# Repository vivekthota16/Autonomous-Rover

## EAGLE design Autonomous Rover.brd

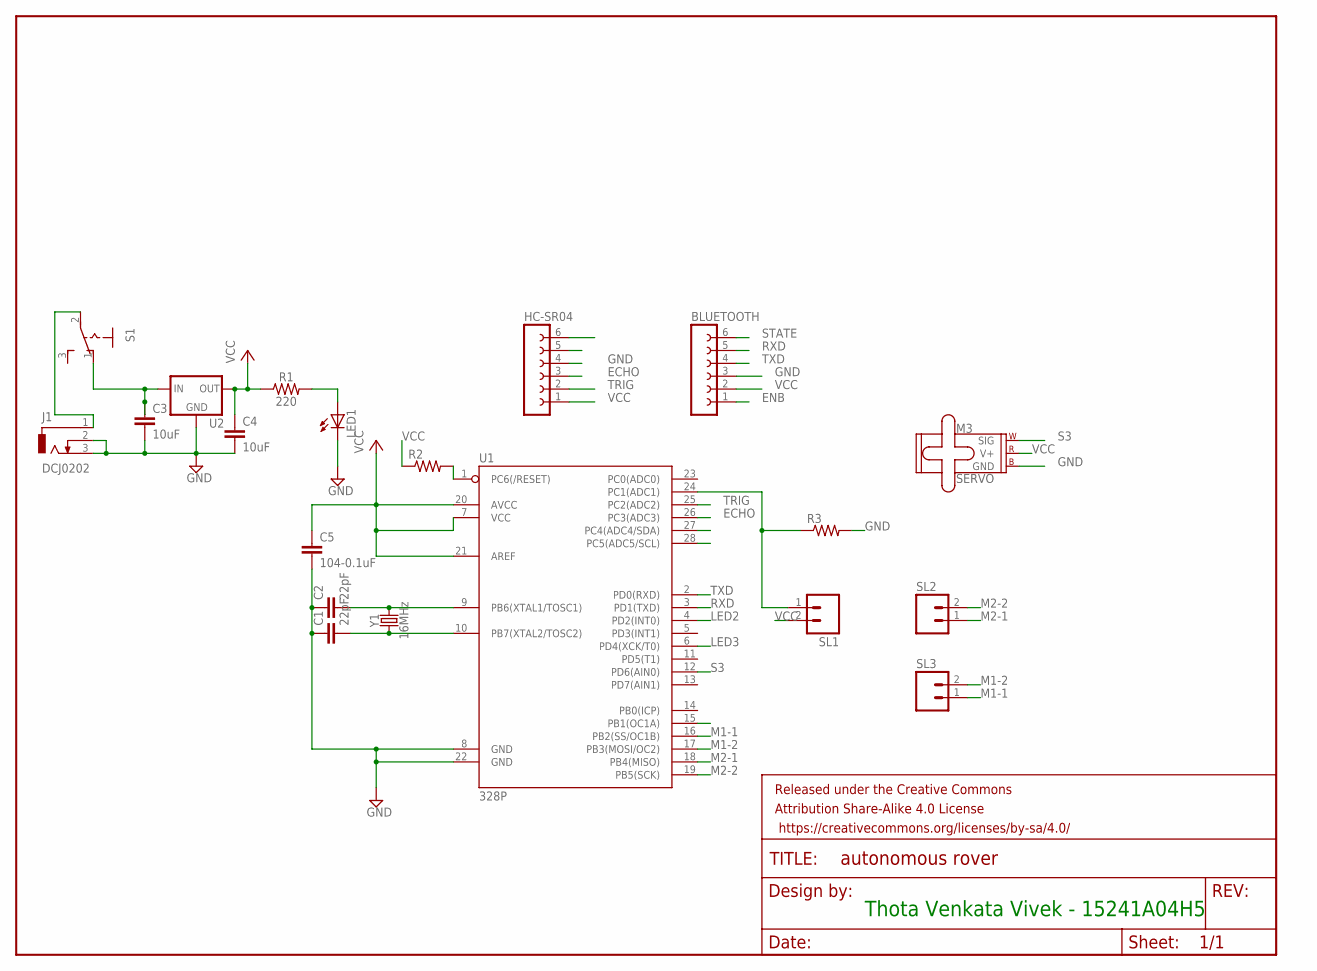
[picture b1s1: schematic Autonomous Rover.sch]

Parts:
BLUETOOTH: FE06-1; FE06
C1, C2: 22pF; C2.5-3
C3, C4: 10uF; C2.5-3
C5: 104-0.1uF; C2.5-3
FRAME1: FRAME-LETTER; CREATIVE_COMMONS
HC-SR04: FE06-1; FE06
J1: DCJ0202
LED1: LED3MM
M3: SERVO; 1X03
R1: 220; AXIAL-0.3
R2, R3: R-US_0204/7; 0204/7
S1: 255SB
SL1, SL2, SL3: M02; 02P
U1: 328P; DIP28
U2: V_REG_78XX-TO-220; TO-220-ALT
Y1: 16MHz; HC49US

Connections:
ECHO: HC-SR04.3, U1.26 (PC3(ADC3))
ENB: BLUETOOTH.1
GND: BLUETOOTH.3, C1.1, C2.1, C3.2, C4.2, C5.2, HC-SR04.4, HC-SR04.6, J1.2, J1.3, LED1.K (C), M3.3 (GND), R3.2, U1.8 (GND), U1.22 (GND), U2.GND
LED2: U1.4 (PD2(INT0))
LED3: HC-SR04.5, U1.6 (PD4(XCK/T0))
M1-1: SL3.1, U1.16 (PB2(SS/OC1B))
M1-2: SL3.2, U1.17 (PB3(MOSI/OC2))
M2-1: SL2.1, U1.18 (PB4(MISO))
M2-2: SL2.2, U1.19 (PB5(SCK))
unnamed: J1.1, S1.2
unnamed: C2.2, U1.9 (PB6(XTAL1/TOSC1)), Y1.2
unnamed: C3.1, S1.1 (O), U2.IN
unnamed: C1.2, U1.10 (PB7(XTAL2/TOSC2)), Y1.1
unnamed: LED1.A, R1.P$2 (2)
unnamed: R2.2, U1.1 (PC6(/RESET))
unnamed: R3.1, SL1.1, U1.24 (PC1(ADC1))
RXD: BLUETOOTH.5, U1.3 (PD1(TXD))
S3: M3.1 (SIG), U1.12 (PD6(AIN0))
S4: U1.15 (PB1(OC1A))
STATE: BLUETOOTH.6
TRIG: HC-SR04.2, U1.25 (PC2(ADC2))
TXD: BLUETOOTH.4, U1.2 (PD0(RXD))
VCC: BLUETOOTH.2, C4.1, C5.1, HC-SR04.1, M3.2 (V+), R1.P$1 (1), R2.1, SL1.2, U1.7 (VCC), U1.20 (AVCC), U1.21 (AREF), U2.OUT
Y: U1.27 (PC4(ADC4/SDA))
Z: U1.28 (PC5(ADC5/SCL))

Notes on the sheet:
Thota Venkata Vivek - 15241A04H5

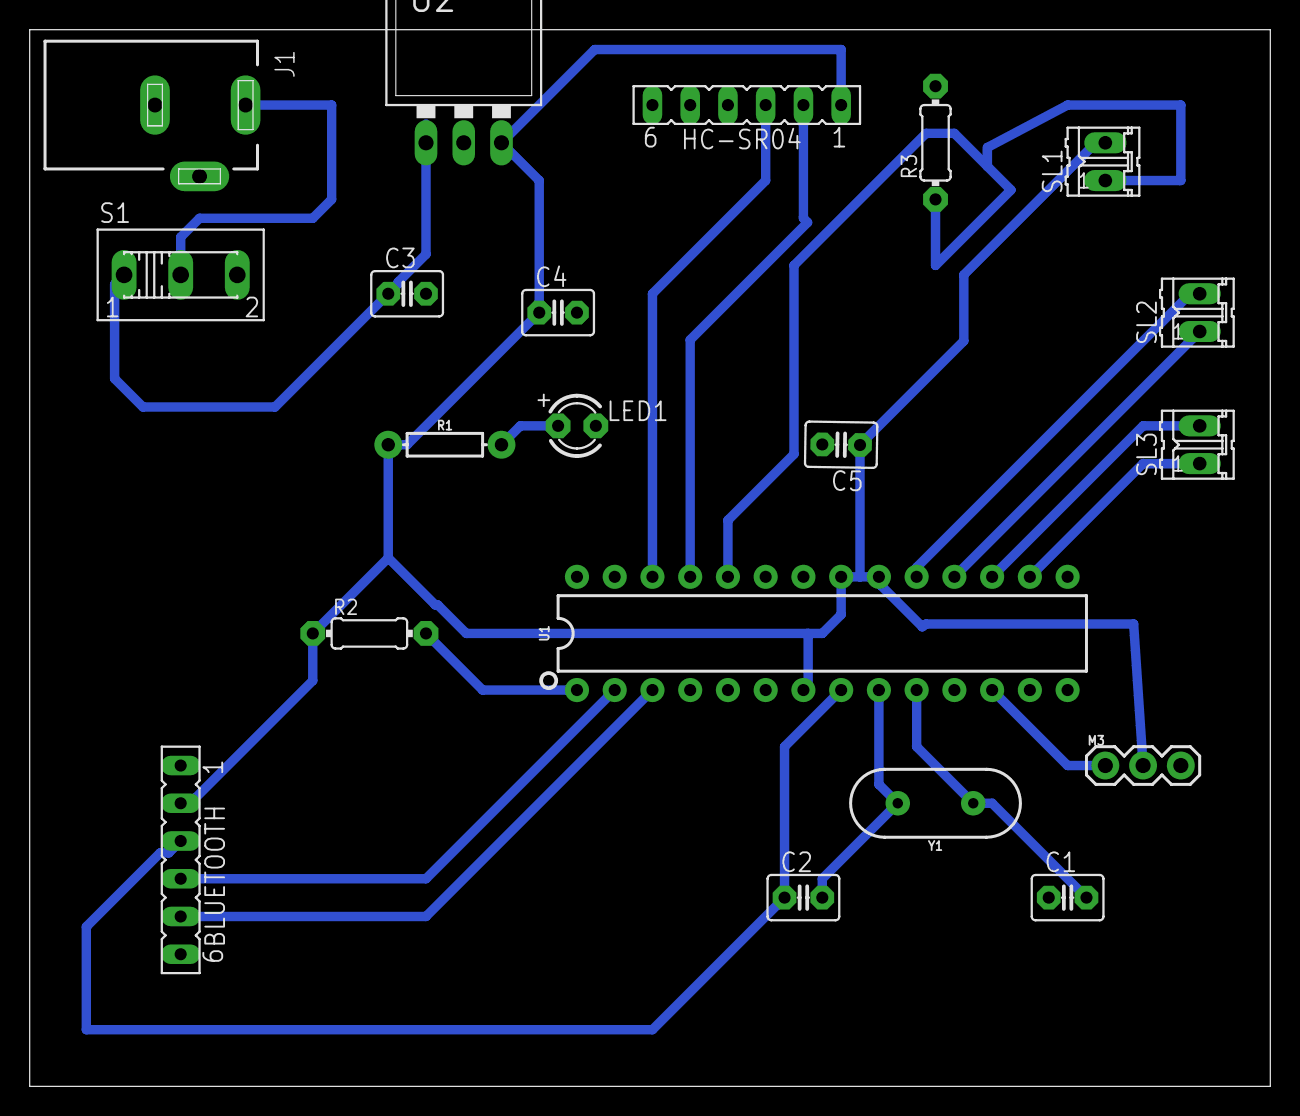
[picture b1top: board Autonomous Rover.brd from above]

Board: 2 copper layers, 83.5 x 71.1 mm, 20 parts (0 on the bottom side), 19 nets.

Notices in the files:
parts and their libraries:
SparkFun-Electromechanical: Licensing: Creative Commons ShareAlike 4.0 International - https://creativecommons.org/licenses/by-sa/4.0
SparkFun-Aesthetics: Released under the Creative Commons Attribution Share-Alike 4.0 License
SparkFun-Aesthetics: https://creativecommons.org/licenses/by-sa/4.0
